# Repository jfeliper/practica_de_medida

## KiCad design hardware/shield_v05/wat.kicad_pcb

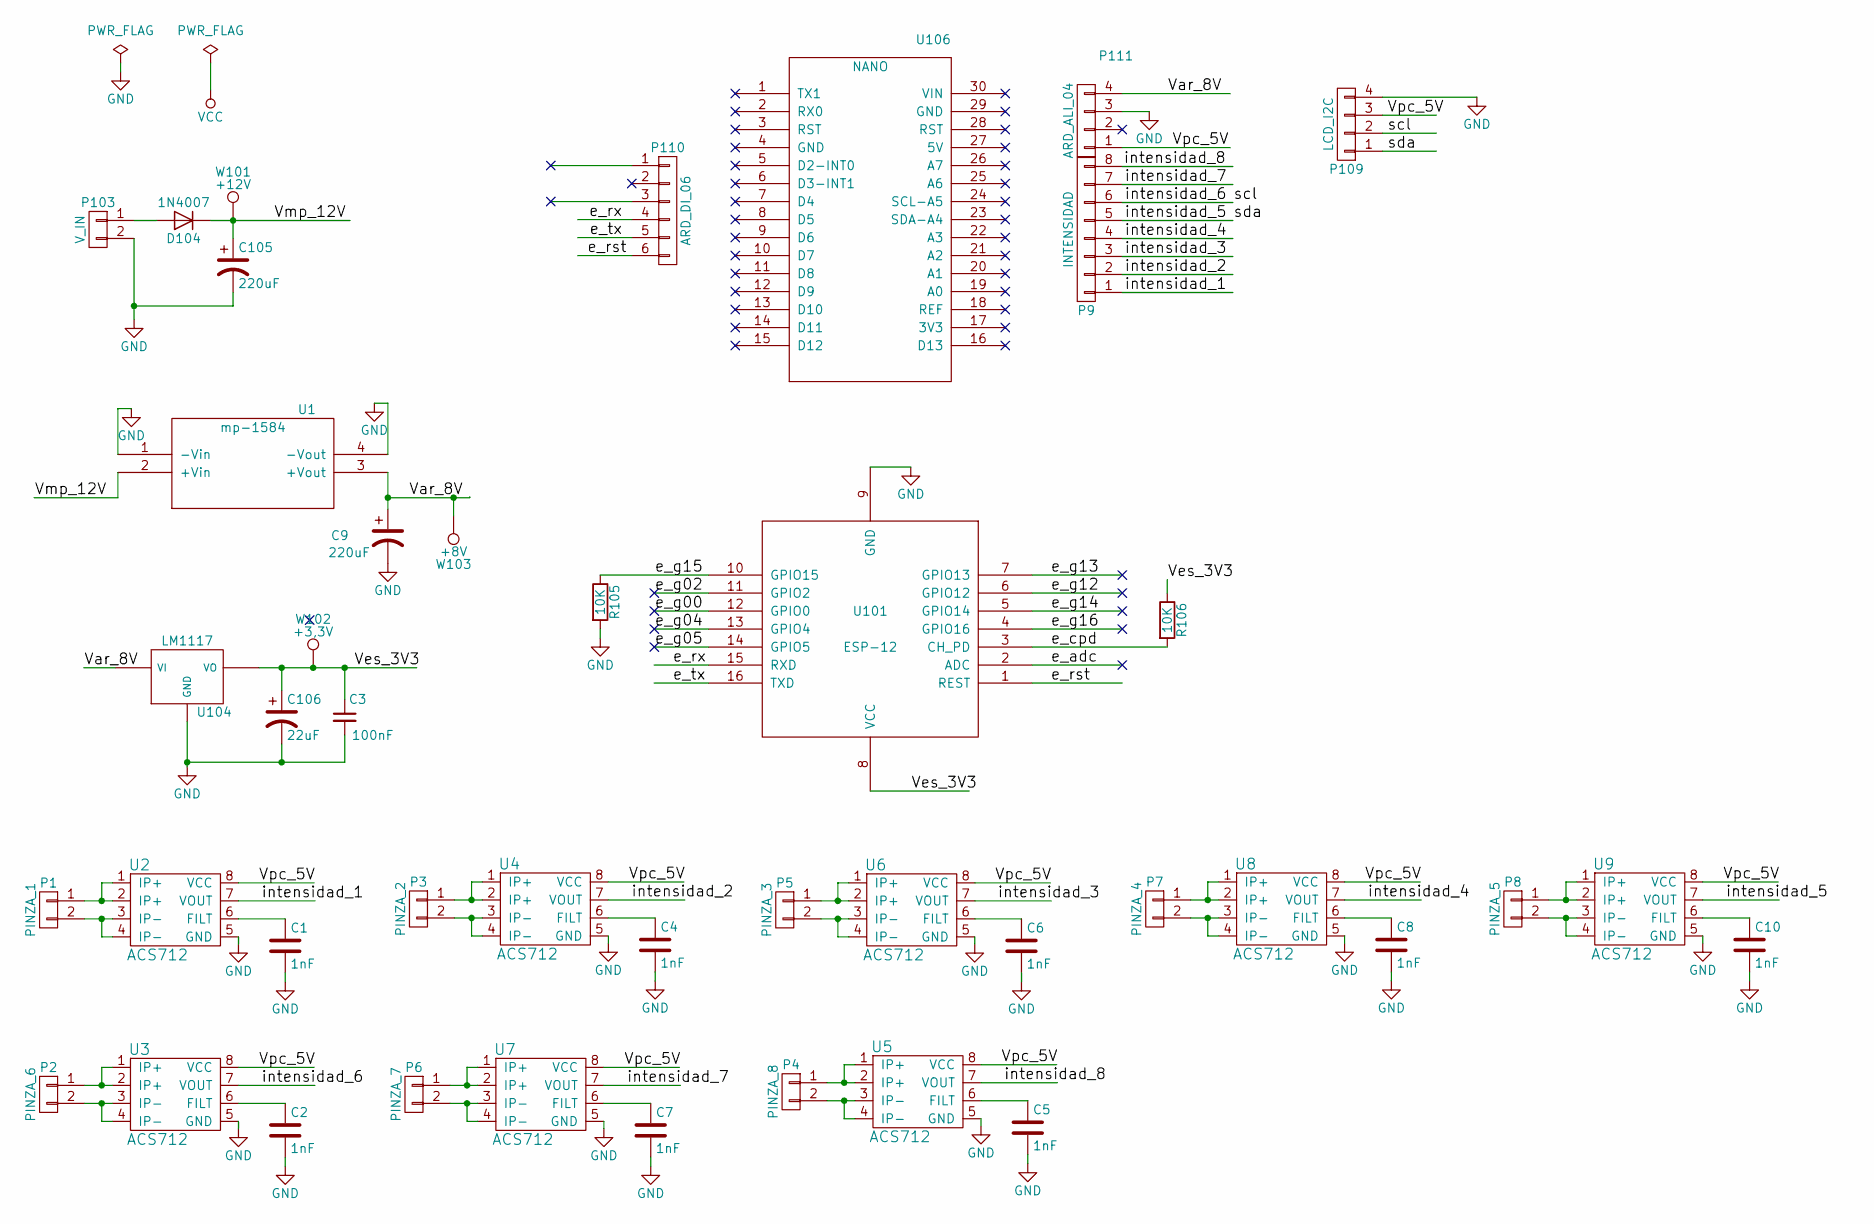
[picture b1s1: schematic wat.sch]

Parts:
C1, C2, C4, C5, C6, C7, C8, C10: 1nF; C_0805_HandSoldering
C3: 100nF; C_Disc_D5.0mm_W2.5mm_P5.00mm
C9, C105: 220uF; CP_Radial_D5.0mm_P2.00mm
C106: 22uF; CP_Radial_D5.0mm_P2.00mm
D104: 1N4007; D_DO-35_SOD27_P10.16mm_Horizontal
P1: PINZA_1; bornier2
P2: PINZA_6; bornier2
P3: PINZA_2; bornier2
P4: PINZA_8; bornier2
P5: PINZA_3; bornier2
P6: PINZA_7; bornier2
P7: PINZA_4; bornier2
P8: PINZA_5; bornier2
P9: INTENSIDAD; Pin_Header_Straight_1x08
P103: V_IN; bornier2
P109: LCD_I2C; Pin_Header_Straight_1x04
P110: ARD_DI_06; Pin_Header_Straight_1x06
P111: ARD_ALI_04; Pin_Header_Straight_1x04
R105, R106: 10K; R_Axial_DIN0207_L6.3mm_D2.5mm_P10.16mm_Horizontal
U1: mp-1584; MP-1584-SD
U2, U3, U4, U5, U6, U7, U8, U9: ACS712
U101: ESP-12; ESP-07v2_pad
U104: LM1117; TO-220-LM117
U106: NANO; arduino_nano
W101: +12V; SolderWirePad_single_0-8mmDrill
W102: +3,3V; SolderWirePad_single_0-8mmDrill
W103: +8V; SolderWirePad_single_0-8mmDrill

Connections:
/Var_8V: C9.1, P111.4, U1.3 (+Vout), U104.VI, W103.1
/Ves_3V3: C3.1, C106.1, R106.1, U101.8 (VCC), U104.VO, W102.1
/Vmp_12V: C105.1, D104.1 (K), U1.2 (+Vin), W101.1
/Vpc_5V: P109.3, P111.1, U2.8 (VCC), U3.8 (VCC), U4.8 (VCC), U5.8 (VCC), U6.8 (VCC), U7.8 (VCC), U8.8 (VCC), U9.8 (VCC)
/e_adc: U101.2 (ADC)
/e_cpd: R106.2, U101.3 (CH_PD)
/e_g00: U101.12 (GPIO0)
/e_g02: U101.11 (GPIO2)
/e_g04: U101.13 (GPIO4)
/e_g05: U101.14 (GPIO5)
/e_g12: U101.6 (GPIO12)
/e_g13: U101.7 (GPIO13)
/e_g14: U101.5 (GPIO14)
/e_g15: R105.1, U101.10 (GPIO15)
/e_g16: U101.4 (GPIO16)
/e_rst: P110.6, U101.1 (REST)
/e_rx: P110.4, U101.15 (RXD)
/e_tx: P110.5, U101.16 (TXD)
/intensidad_1: P9.1, U2.7 (VOUT)
/intensidad_2: P9.2, U4.7 (VOUT)
/intensidad_3: P9.3, U6.7 (VOUT)
/intensidad_4: P9.4, U8.7 (VOUT)
/intensidad_5: P9.5, P109.1, U9.7 (VOUT)
/intensidad_6: P9.6, P109.2, U3.7 (VOUT)
/intensidad_7: P9.7, U7.7 (VOUT)
/intensidad_8: P9.8, U5.7 (VOUT)
GND: C1.2, C2.2, C3.2, C4.2, C5.2, C6.2, C7.2, C8.2, C9.2, C10.2, C105.2, C106.2, P103.2, P109.4, P111.3, R105.2, U1.1 (-Vin), U1.4 (-Vout), U2.5 (GND), U3.5 (GND), U4.5 (GND), U5.5 (GND), U6.5 (GND), U7.5 (GND), U8.5 (GND), U9.5 (GND), U101.9 (GND), U104.GND
unnamed: C1.1, U2.6 (FILT)
unnamed: C2.1, U3.6 (FILT)
unnamed: C4.1, U4.6 (FILT)
unnamed: C5.1, U5.6 (FILT)
unnamed: C6.1, U6.6 (FILT)
unnamed: C7.1, U7.6 (FILT)
unnamed: C8.1, U8.6 (FILT)
unnamed: C10.1, U9.6 (FILT)
unnamed: D104.2 (A), P103.1
unnamed: P1.1, U2.1 (IP+), U2.2 (IP+)
unnamed: P1.2, U2.3 (IP-), U2.4 (IP-)
unnamed: P2.1, U3.1 (IP+), U3.2 (IP+)
unnamed: P2.2, U3.3 (IP-), U3.4 (IP-)
unnamed: P3.1, U4.1 (IP+), U4.2 (IP+)
unnamed: P3.2, U4.3 (IP-), U4.4 (IP-)
unnamed: P4.1, U5.1 (IP+), U5.2 (IP+)
unnamed: P4.2, U5.3 (IP-), U5.4 (IP-)
unnamed: P5.1, U6.1 (IP+), U6.2 (IP+)
unnamed: P5.2, U6.3 (IP-), U6.4 (IP-)
unnamed: P6.1, U7.1 (IP+), U7.2 (IP+)
unnamed: P6.2, U7.3 (IP-), U7.4 (IP-)
unnamed: P7.1, U8.1 (IP+), U8.2 (IP+)
unnamed: P7.2, U8.3 (IP-), U8.4 (IP-)
unnamed: P8.1, U9.1 (IP+), U9.2 (IP+)
unnamed: P8.2, U9.3 (IP-), U9.4 (IP-)

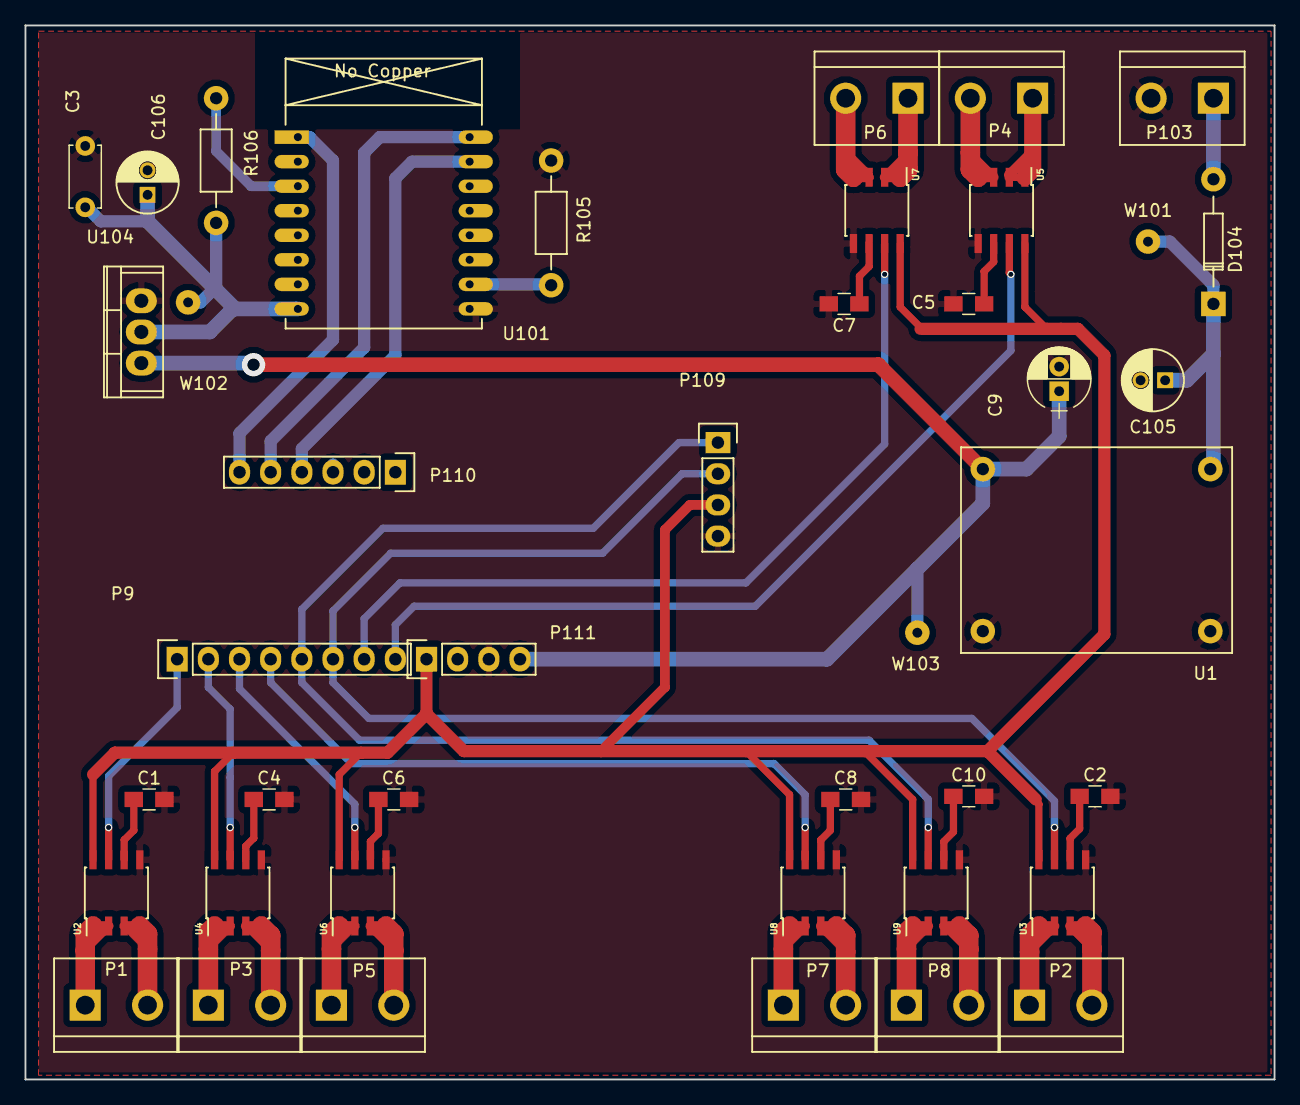
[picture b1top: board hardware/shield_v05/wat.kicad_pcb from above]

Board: 2 copper layers, 101.8 x 85.9 mm, 42 parts (0 on the bottom side), 43 nets.

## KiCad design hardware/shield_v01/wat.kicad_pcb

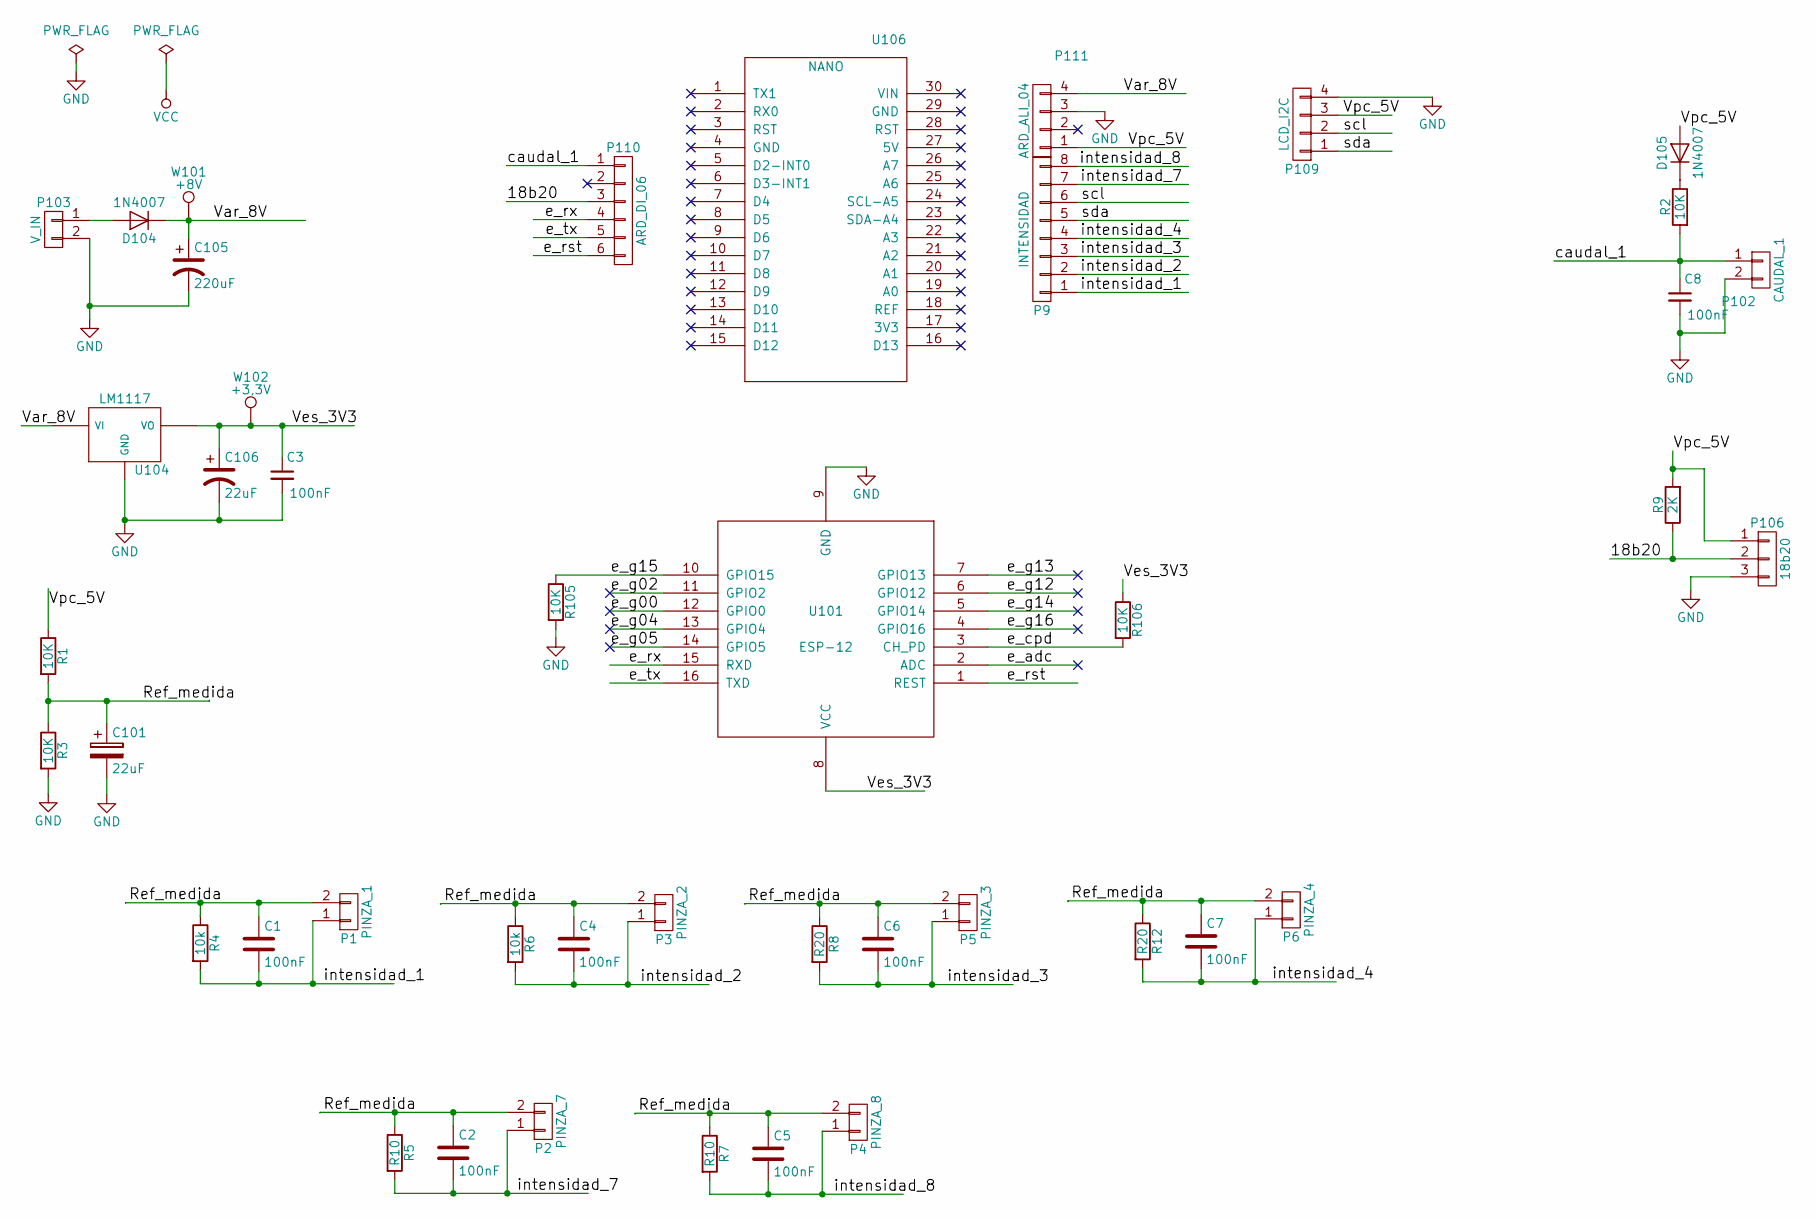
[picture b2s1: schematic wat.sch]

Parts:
C1, C2, C3, C4, C5, C6, C7, C8: 100nF; C_Disc_D5.0mm_W2.5mm_P5.00mm
C101, C106: 22uF; CP_Radial_D5.0mm_P2.00mm
C105: 220uF; CP_Radial_D5.0mm_P2.00mm
D104, D105: 1N4007; Diode_DO-35_SOD27_Horizontal_RM10
P1: PINZA_1; bornier2
P2: PINZA_7; bornier2
P3: PINZA_2; bornier2
P4: PINZA_8; bornier2
P5: PINZA_3; bornier2
P6: PINZA_4; bornier2
P9: INTENSIDAD; Pin_Header_Straight_1x08
P102: CAUDAL_1; bornier2
P103: V_IN; bornier2
P106: 18b20; bornier3
P109: LCD_I2C; Pin_Header_Straight_1x04
P110: ARD_DI_06; Pin_Header_Straight_1x06
P111: ARD_ALI_04; Pin_Header_Straight_1x04
R1, R2, R3, R105, R106: 10K; Resistor_Horizontal_RM10mm
R4, R6: 10k; Resistor_Horizontal_RM10mm
R5, R7: R10; Resistor_Horizontal_RM10mm
R8, R12: R20; Resistor_Horizontal_RM10mm
R9: 2K; Resistor_Horizontal_RM10mm
U101: ESP-12; ESP-07v2_pad
U104: LM1117; TO-220-LM117
U106: NANO; arduino_nano
W101: +8V; SolderWirePad_single_0-8mmDrill
W102: +3,3V; SolderWirePad_single_0-8mmDrill

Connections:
/18b20: P106.2, P110.3, R9.1
/Ref_medida: C1.1, C2.1, C4.1, C5.1, C6.1, C7.1, C101.1, P1.2, P2.2, P3.2, P4.2, P5.2, P6.2, R1.2, R3.1, R4.1, R5.1, R6.1, R7.1, R8.1, R12.1
/Var_8V: C105.1, D104.1 (K), P111.4, U104.VI, W101.1
/Ves_3V3: C3.1, C106.1, R106.1, U101.8 (VCC), U104.VO, W102.1
/Vpc_5V: D105.2 (A), P106.1, P109.3, P111.1, R1.1, R9.2
/caudal_1: C8.1, P102.1, P110.1, R2.2
/e_adc: U101.2 (ADC)
/e_cpd: R106.2, U101.3 (CH_PD)
/e_g00: U101.12 (GPIO0)
/e_g02: U101.11 (GPIO2)
/e_g04: U101.13 (GPIO4)
/e_g05: U101.14 (GPIO5)
/e_g12: U101.6 (GPIO12)
/e_g13: U101.7 (GPIO13)
/e_g14: U101.5 (GPIO14)
/e_g15: R105.1, U101.10 (GPIO15)
/e_g16: U101.4 (GPIO16)
/e_rst: P110.6, U101.1 (REST)
/e_rx: P110.4, U101.15 (RXD)
/e_tx: P110.5, U101.16 (TXD)
/intensidad_1: C1.2, P1.1, P9.1, R4.2
/intensidad_2: C4.2, P3.1, P9.2, R6.2
/intensidad_3: C6.2, P5.1, P9.3, R8.2
/intensidad_4: C7.2, P6.1, P9.4, R12.2
/intensidad_7: C2.2, P2.1, P9.7, R5.2
/intensidad_8: C5.2, P4.1, P9.8, R7.2
/scl: P9.6, P109.2
/sda: P9.5, P109.1
GND: C3.2, C8.2, C101.2, C105.2, C106.2, P102.2, P103.2, P106.3, P109.4, P111.3, R3.2, R105.2, U101.9 (GND), U104.GND
unnamed: D104.2 (A), P103.1
unnamed: D105.1 (K), R2.1

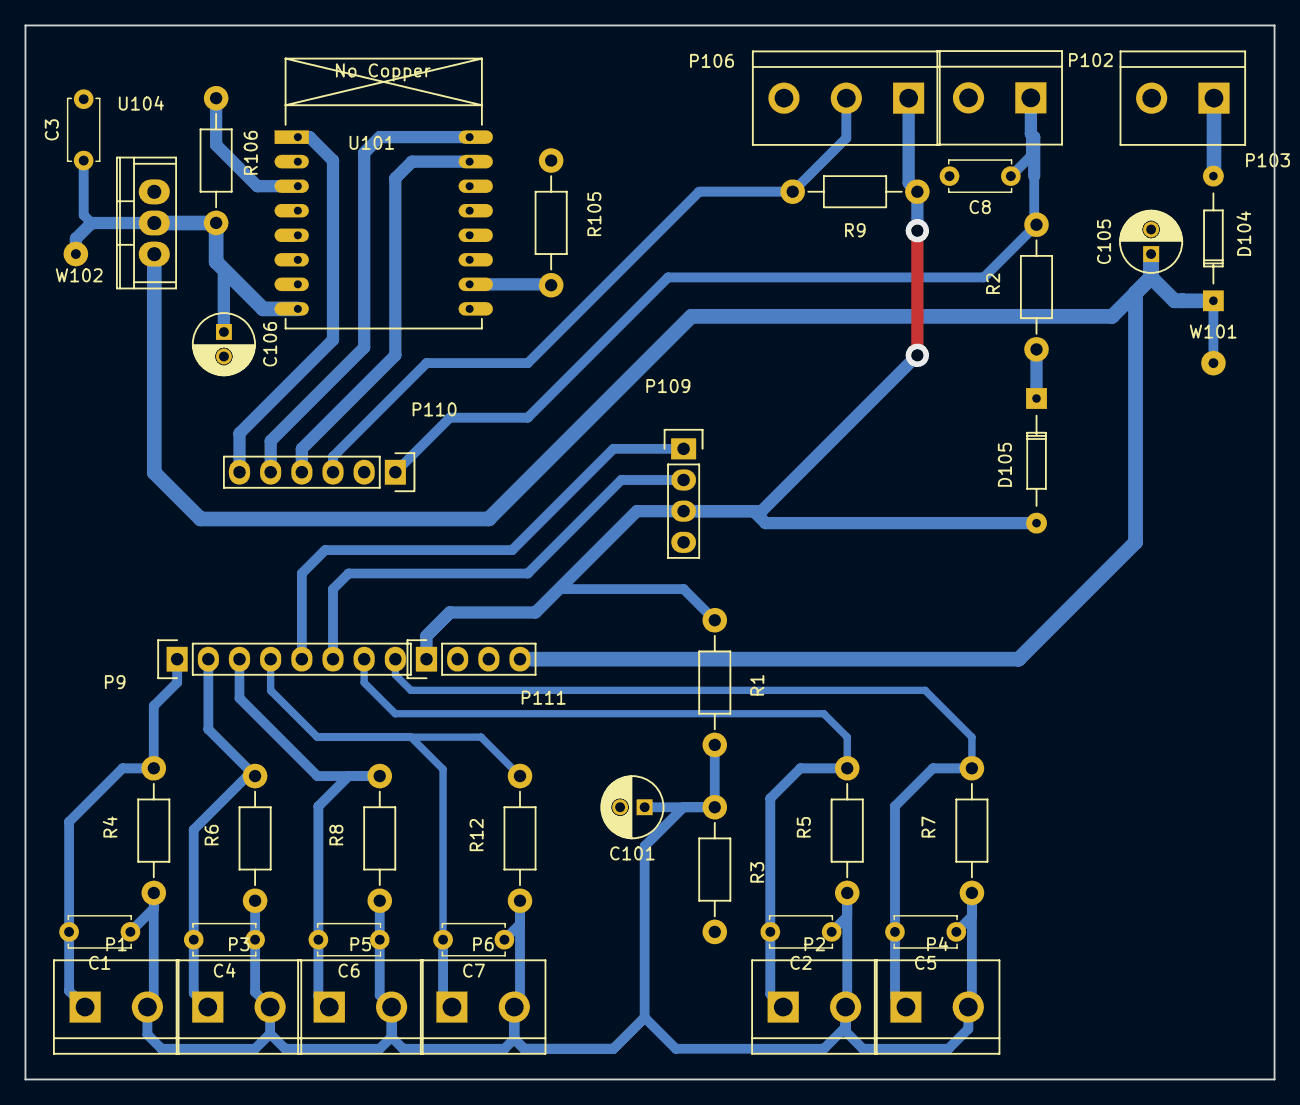
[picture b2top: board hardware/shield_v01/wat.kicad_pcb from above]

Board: 2 copper layers, 101.8 x 85.9 mm, 42 parts (0 on the bottom side), 22 nets.

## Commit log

2017-09-05 hardware de medida
2017-09-05 desrrollo pcb
2017-09-07 desarrollo pcb v0
2017-09-11 pcb simplificar a 6 medidas
2017-09-22 pcb cambio de valores de resistencias de carga
2017-09-25 pcb. circuit image
2017-11-13 arduino firmware included
2017-11-17 hardware a fabricar
2017-12-05 cambios menores
2017-12-05 hw resistencia de 20W
2017-12-11 pcb version con acs712
2017-12-11 pcb v5 gerbers
2018-01-04 primera version presentacion azucarera
2018-01-13 cambios menores pcb. Borrar linea de referencia
2018-01-16 menores
2018-02-07 borrar
2018-02-07 transformadores intensidad 5A
2018-02-07 solo hw con acs712
2018-03-07 calculo factor multiplicador
2018-04-29 diferenciar con y sin display
2018-05-18 cambio de la presentacion a su propio proyecto
2018-05-19 configuracion pinzas azucarera
2018-06-14 cambios para practica
